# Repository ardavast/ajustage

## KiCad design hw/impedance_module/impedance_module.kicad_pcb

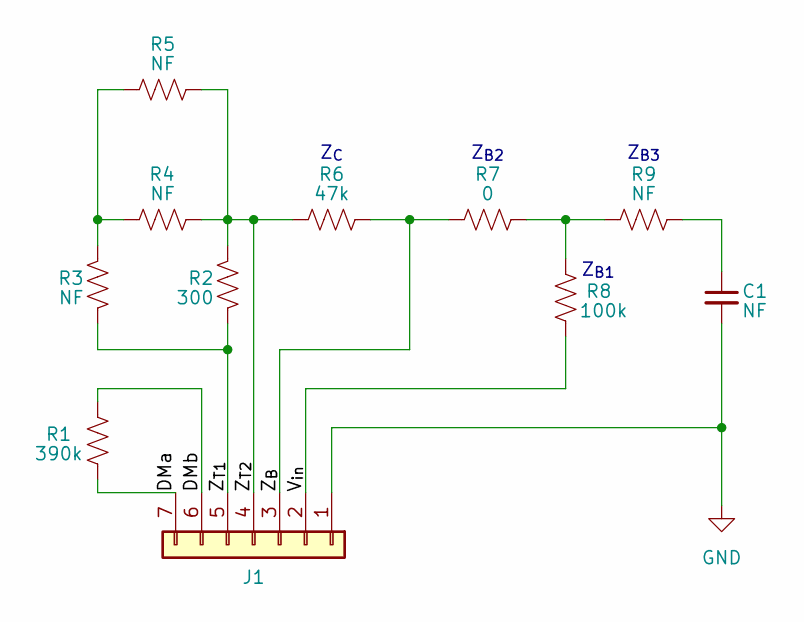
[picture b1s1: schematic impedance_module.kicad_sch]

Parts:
C1: NF; C_0805_2012Metric
J1: Conn_01x07; PinHeader_1x07_P2.54mm_Horizontal
R1: 390k; R_0805_2012Metric
R2: 300; R_0805_2012Metric
R3, R4, R5, R9: NF; R_0805_2012Metric
R6: 47k; R_0805_2012Metric
R7: 0; R_0805_2012Metric
R8: 100k; R_0805_2012Metric

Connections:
/DMa: J1.7, R1.1
/DMb: J1.6, R1.2
/V_{in}: J1.2, R8.2
/Z_{B}: J1.3, R6.2, R7.1
/Z_{T1}: J1.5, R2.2, R3.2
/Z_{T2}: J1.4, R2.1, R4.2, R5.2, R6.1
GND: C1.2, J1.1
unnamed: C1.1, R9.2
unnamed: R3.1, R4.1, R5.1
unnamed: R7.2, R8.1, R9.1

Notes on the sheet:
Z_{C}
Z_{B2}
Z_{B3}
Z_{B1}

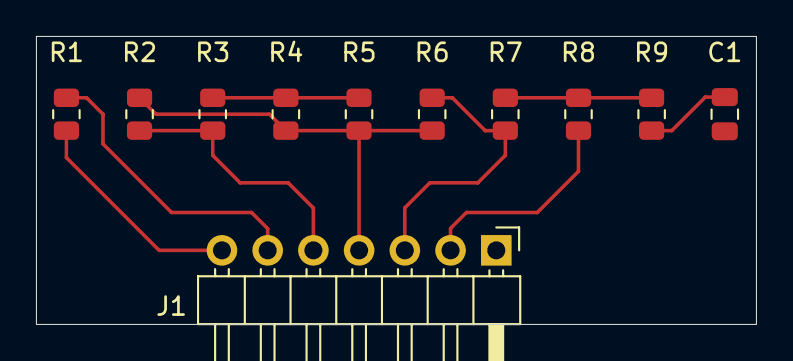
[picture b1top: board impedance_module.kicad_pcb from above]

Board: 2 copper layers, 40.0 x 16.0 mm, 11 parts (0 on the bottom side), 10 nets.

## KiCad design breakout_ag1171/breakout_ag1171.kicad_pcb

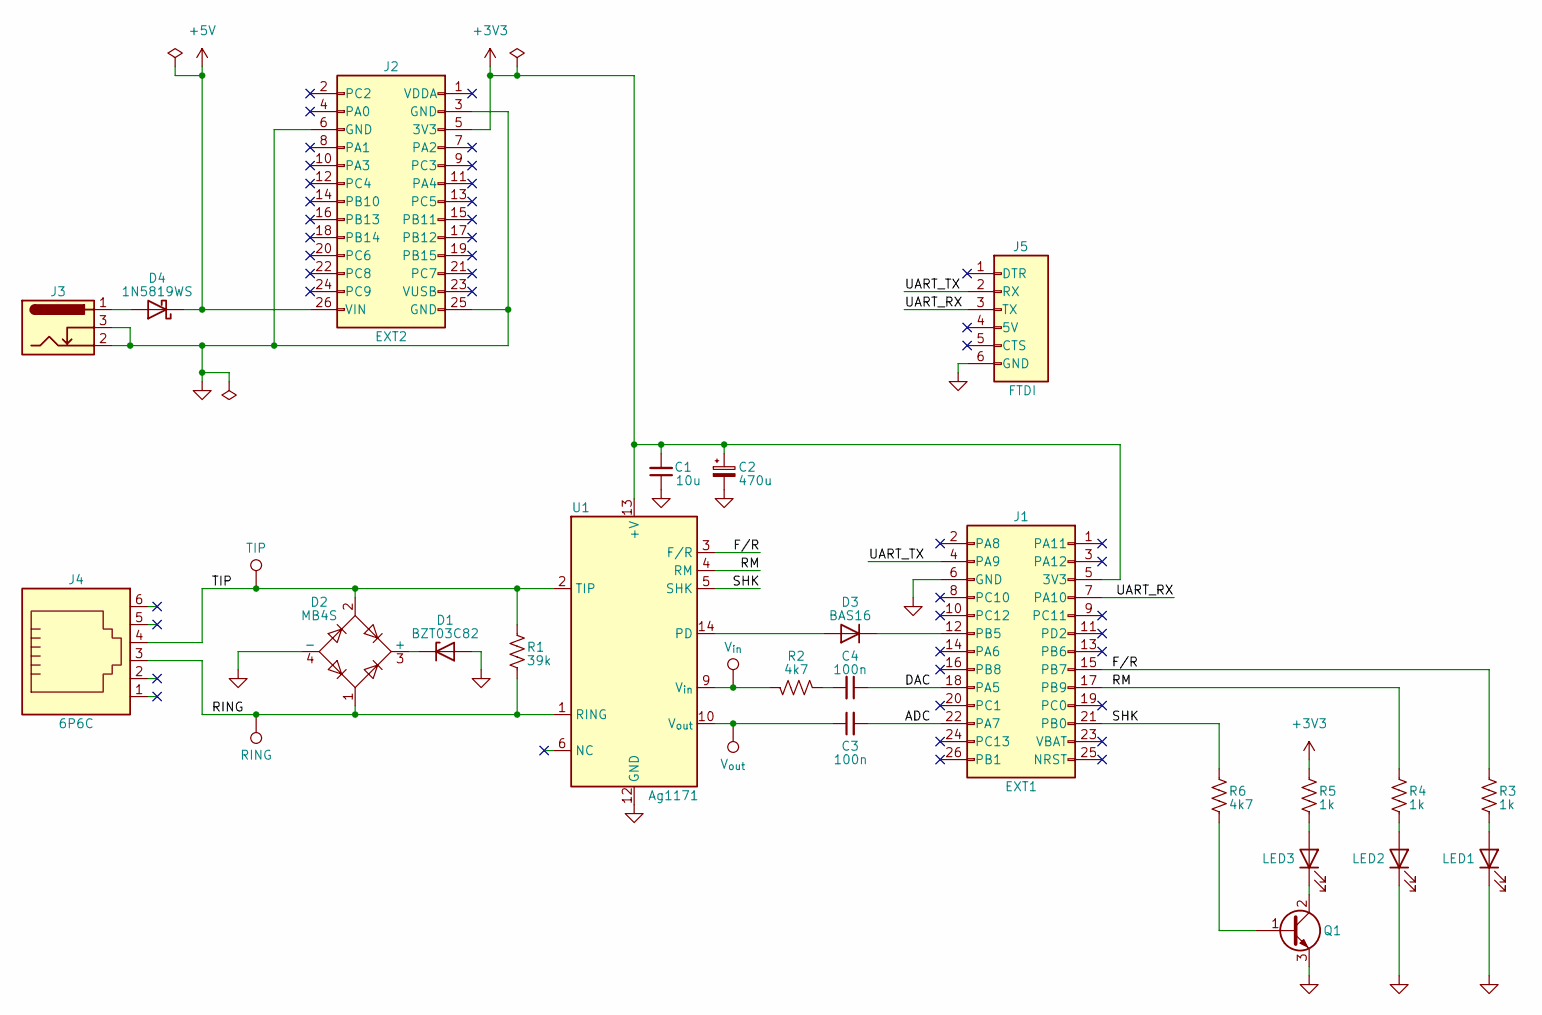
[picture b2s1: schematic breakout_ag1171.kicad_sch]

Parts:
C1: 10u; C_0402_1005Metric; LCSC C76991
C2: 470u; CP_Elec_8x10; LCSC C445481
C3, C4: 100n; C_0402_1005Metric; LCSC C71629
D1: BZT03C82; D_DO-35_SOD27_P12.70mm_Horizontal
D2: MB4S; TO-269AA; LCSC C145443
D3: BAS16; D_SOD-323; LCSC C131148
D4: 1N5819WS; D_SOD-323; LCSC C191023
J1: EXT1; PinSocket_2x13_P2.54mm_Vertical
J2: EXT2; PinSocket_2x13_P2.54mm_Vertical
J3: Barrel_Jack_Switch; BarrelJack_GCT_DCJ200-10-A_Horizontal
J4: 6P6C; RJ25_Wayconn_MJEA-660X1_Horizontal
J5: FTDI; PinHeader_1x06_P2.54mm_Vertical
LED1: F/R; LED_0805_2012Metric; LCSC C2295
LED2: RM; LED_0805_2012Metric; LCSC C2296
LED3: SHK; LED_0805_2012Metric; LCSC C2297
Q1: Q_NPN_BCE; SOT-23; LCSC C20526
R1: 39k; R_0805_2012Metric; LCSC C25826
R2: 4k7; R_0805_2012Metric; LCSC C17673
R3, R4, R5: 1k; R_0805_2012Metric; LCSC C17513
R6: 4k7; R_0805_2012Metric; LCSC C17513
TP1: TIP; Pin_D1.0mm_L10.0mm_LooseFit
TP2: RING; Pin_D1.0mm_L10.0mm_LooseFit
TP3: V_{out}; Pin_D1.0mm_L10.0mm_LooseFit
TP4: V_{in}; Pin_D1.0mm_L10.0mm_LooseFit
U1: Ag1171

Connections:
+3V3: C1.2, C2.1, J1.5 (3V3), J2.5 (3V3), R5.2, U1.13 (+V)
+5V: D4.1 (K), J2.26 (VIN)
/ADC: C3.2, J1.22 (PA7)
/DAC: C4.1, J1.18 (PA5)
/F/R: J1.15 (PB7), R3.2, U1.3 (F/R)
/RING: D2.1, J4.3, R1.1, TP2.1, U1.1 (RING)
/RM: J1.17 (PB9), R4.2, U1.4 (RM)
/SHK: J1.21 (PB0), R6.2, U1.5 (SHK)
/TIP: D2.2, J4.4, R1.2, TP1.1, U1.2 (TIP)
/UART_RX: J1.7 (PA10), J5.3 (TX)
/UART_TX: J1.4 (PA9), J5.2 (RX)
GND: C1.1, C2.2, D1.2 (A), D2.4 (-), J1.6 (GND), J2.3 (GND), J2.6 (GND), J2.25 (GND), J3.2, J3.3, J5.6 (GND), LED1.1 (K), LED2.1 (K), Q1.3 (E), U1.12 (GND)
unnamed: C4.2, R2.1
unnamed: D1.1 (K), D2.3 (+)
unnamed: D3.2 (A), U1.14 (PD)
unnamed: D3.1 (K), J1.12 (PB5)
unnamed: D4.2 (A), J3.1
unnamed: LED1.2 (A), R3.1
unnamed: LED2.2 (A), R4.1
unnamed: LED3.2 (A), R5.1
unnamed: LED3.1 (K), Q1.2 (C)
unnamed: Q1.1 (B), R6.1
unnamed: R2.2, TP4.1, U1.9 (V_{in})
unnamed: C3.1, TP3.1, U1.10 (V_{out})

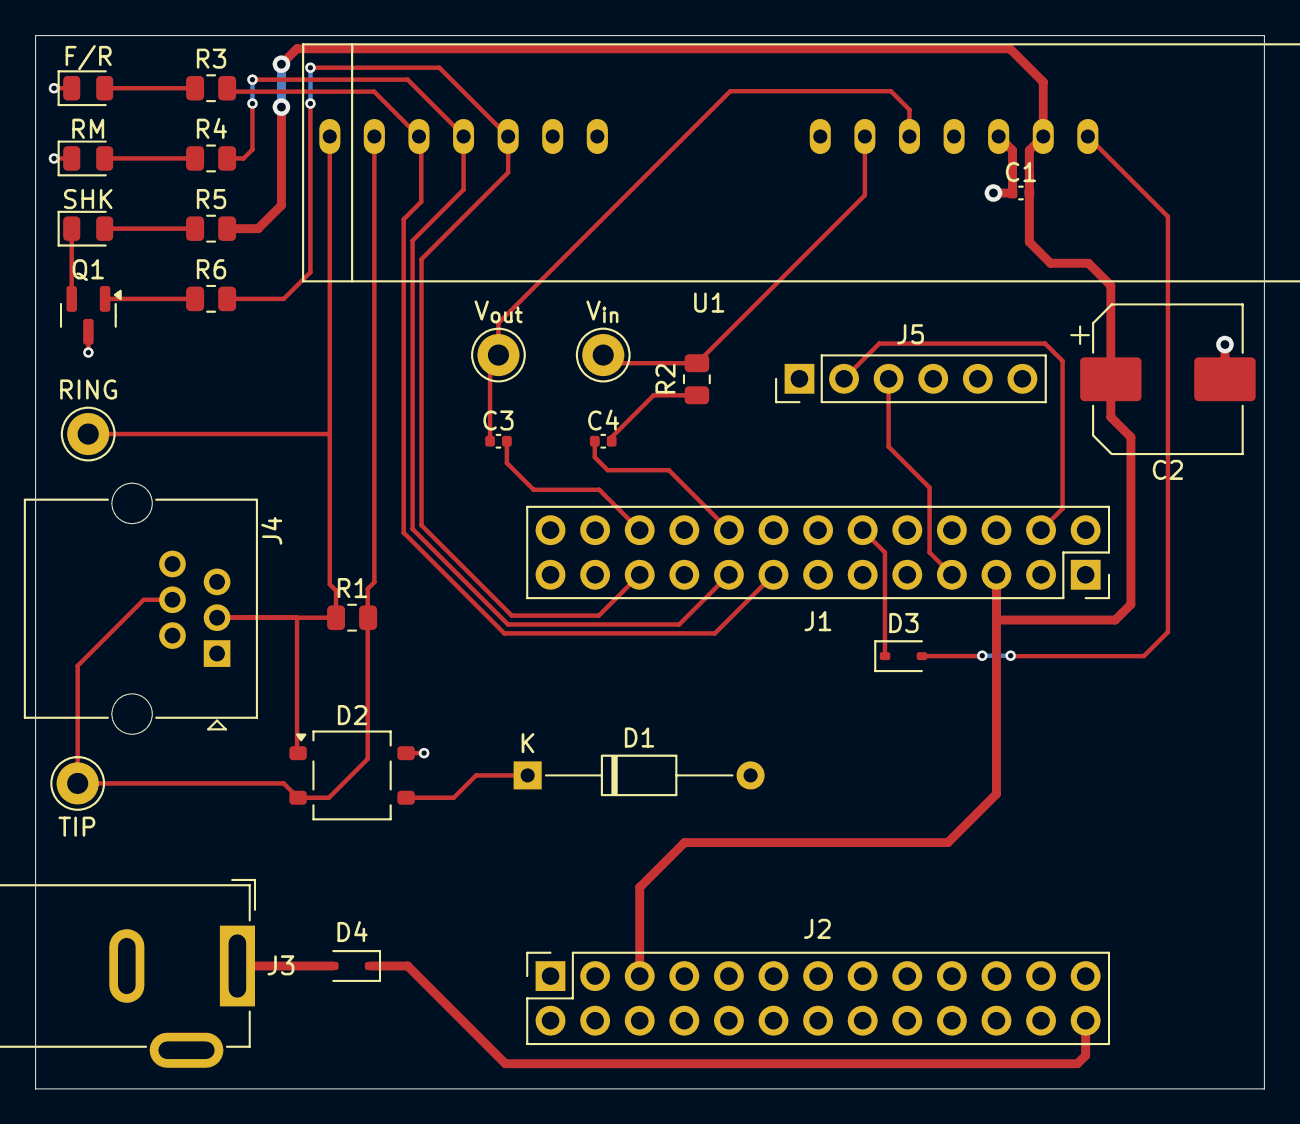
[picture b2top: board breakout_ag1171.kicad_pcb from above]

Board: 2 copper layers, 70.0 x 60.0 mm, 28 parts (0 on the bottom side), 24 nets.

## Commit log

2024-09-18 Add ringer
2024-09-18 Pin freertos at V11.1.0
2024-09-25 Add 440Hz dial tone test
2024-09-27 Do not set regs to their default values
2024-09-27 Trigger the DAC with a timer interrupt
2024-09-28 Use DMA for playing the dialtone
2024-09-29 Play audio over serial
2024-10-10 Breakout for Ag1171/STM32H405/FTDI Basic
2024-10-11 Add KiBot and pdf outputs for breakout_ag1171
2024-10-12 Fix wrong audio channel connections
2024-11-02 Exclude U1 from BOM
2024-11-09 Add dtmf_tx
2024-11-09 Use DAC channel 2
2024-11-24 Clean up the repo
2025-04-22 Add usb_dac (no circular buffer)
2025-04-24 Simplify audio_rx_cb
